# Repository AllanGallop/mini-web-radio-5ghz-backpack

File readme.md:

# Mini Web Radio 3 — 5 GHz Backpack

This project started when the hospital switched off its 2.4 GHz Wi-Fi. The Mini Web Radio was built around an ESP32-S3, which could no longer connect to the network. We also had 200 populated boards already fabricated, so replacing the main board was something I wanted to avoid.

The result is a backpack for [Mini Web Radio v3](https://github.com/AllanGallop/mini-web-radio-3). An ESP32-C5 handles the network connection, while the original S3 keeps doing the audio work. The main PCB, controls and audio hardware all stay in place.

<p align="center">
  
</p>

## Keeping the S3

The S3 had already proved itself in the radio. It could decode the stream, feed the audio output and respond to the controls, with two processor cores and external RAM to help share the work. There was a working design and a working audio stack, so I wanted to keep as much of that as possible.

Unfortunately, its Wi-Fi hardware only supports 2.4 GHz and once that band disappeared from the hospital network, the radio needed another way to connect.

The ESP32-C5 offered the missing connectivity. The question was whether it should replace the S3 or work alongside it.

## Could the C5 do everything?

Replacing the S3 with a C5 would have made for a tidier design, but it would also have meant taking on a much larger software job.

The radio uses [a fork of ESP32-audioI2S](https://github.com/AllanGallop/ESP32-audioI2S), which is designed for multicore ESP32 devices. The C5 has only one app core. It does have a separate low-power processor, but it can't serve as the second application core the audio library expects.

Receiving a stream is only part of the job: the radio also has to buffer and decode it, keep the I²S output supplied, and respond when someone turns the dial. Moving everything onto the C5 would mean porting or replacing the audio stack and working out how to keep those jobs running reliably on one application core.

Memory is another constraint, although it is easy to overstate it. The C5 has less internal SRAM than the S3. Adding RAM can help with buffers; it doesn't make software written for two application cores work on one.

Keeping the S3 and giving the C5 responsibility for handling connectivity and fetching the stream was a more manageable change.

### Separate chips, separate memory

Using both processors doesn't give the radio a single shared pool of RAM. Each chip still has its own memory, and anything needed by the other has to be sent over SPI.

```mermaid
flowchart TB
  subgraph C5["ESP32-C5: network side"]
    CCPU["One application core"]
    CRAM["384 KB internal HP SRAM"]
    CPS["External PSRAM supported"]
    CCPU --- CRAM
    CCPU --- CPS
  end
  subgraph S3["ESP32-S3: audio side"]
    SCPU["Two application cores"]
    SRAM["512 KB internal SRAM"]
    SPS["External PSRAM supported"]
    SCPU --- SRAM
    SCPU --- SPS
  end
  CCPU <-->|"SPI"| SCPU
```

I did consider whether the two chips could share external PSRAM, but coordinating access would have added far too much complexity for this upgrade. Keeping their memory separate and passing the stream over SPI was a much more practical approach.

## Why not attach an SDIO radio?

Another option was to leave the S3 running the whole application and connect a 5 GHz Wi-Fi module over SDIO. That would have avoided changing where the stream was fetched, but getting it into the existing software environment was the sticking point.

The radio is built with PlatformIO and the Arduino framework. An SDIO module needs a host driver, support for the module's firmware, and a way into the networking APIs the application uses. Finding a module with a Linux driver wouldn't solve those problems for this build.

There are supported approaches, including [Espressif's ESP-Hosted](https://github.com/espressif/esp-hosted-mcu), which can connect a C5 over SDIO. Adopting one would still mean getting the host driver, Arduino core, underlying ESP-IDF version and audio dependencies working together.

There was also the question of how much work would remain on the S3. In the conventional hosted arrangement, the external chip handles Wi-Fi while TCP/IP and sockets remain on the host. The S3 would still be fetching the stream and handling HTTP, or TLS where required, alongside decoding and playback. Replacing the native Wi-Fi stack would remove some work too, and the only reliable answer would come from profiling the complete implementation. But it offered less separation of the networking and audio workloads than letting the C5 fetch the stream itself.

The choice of SPI wasn't what made the offload useful. The useful part was being able to hand the networking job to the C5 and give the S3 a stream of compressed audio bytes to play. There would still be two firmware builds and a protocol to maintain, but I could keep the interface focused on what this radio needed and make it easier for other builders to implement.

## Getting the two chips to cooperate

With the work split between the processors, the next problem was keeping audio moving between them. The C5 receives data in bursts from the network and the S3 has to turn it into a continuous audio output.

The backpack connects them over SPI, using `MOSI`, `MISO`, `CLK` and `CS`, with a separate `RDY` line for coordinating transfers. There is no wireless pairing between the chips: they are physically connected by a flex PCB.

The stream crosses that connection while it is still compressed. Decoding happens on the S3, and the resulting PCM samples go to the DAC over I²S.

```mermaid
flowchart TB
  NET["Internet radio stream"]
  subgraph C5["ESP32-C5"]
    WIFI["5 GHz Wi-Fi and network reception"]
    TX["Stream bytes buffered for transfer"]
    WIFI --> TX
  end
  subgraph S3["ESP32-S3"]
    RX["Received stream buffer"]
    DEC["Compressed audio decoder"]
    PCM["PCM output buffers"]
    RX --> DEC --> PCM
  end
  DAC["PCM5102A DAC"]
  AMP["TDA1308 headphone driver"]
  NET --> WIFI
  TX -->|"SPI: one 1033-byte frame"| RX
  TX -.->|"READY while the chunk queue has audio"| RX
  PCM -->|"I²S: PCM samples"| DAC
  DAC -->|"Analogue stereo"| AMP
```

Getting bytes across SPI is only the beginning. A faster clock moves a burst sooner, and it does nothing for a socket that has stopped. The two images have to agree on a fixed transfer, which of those bytes are audio, and what happens when a queue is full or a frame does not check out.

### Keeping the stream moving

An HTTP read, an SPI transfer and an MP3 frame are three different things. The C5 collects stream bytes and packages them for the link; the S3 puts the received audio into a ring buffer for the decoder. Those buffers give each processor some breathing room when the other is busy.

One detail that matters is what `READY` actually means. It tells the S3 that the C5 has queued audio, rather than telling the C5 that the S3 has space. If the S3's ring buffer fills up, the current implementation drops the incoming chunk. When the C5's own queue fills, its HTTP task waits instead, allowing the network connection to slow down.

That distinction is worth making explicit: there is buffering on both sides, but there isn't end-to-end flow control protecting the S3's ring buffer.

### Current limitations

The link checks frames for corruption and tracks sequence gaps, but it doesn't request retransmission of missing audio. A full S3 ring buffer causes a whole chunk to be dropped. Reconnecting the stream also doesn't clear the queued audio or insert a restart marker, so bytes from the previous connection can be followed by bytes from the new one. These are limitations of the current firmware rather than guarantees of seamless recovery.

<details>
<summary>Protocol details: frame layout, queues and recovery</summary>

### SPI frame layout

Both firmware images declare the same packed `Frame`: a 9-byte header followed by a 1024-byte payload. Every SPI transfer clocks all **1033 bytes**, even when only part of the payload contains audio. The `len` field identifies the valid audio bytes; the unused payload is zero-filled.

| Byte offset | Field | Size | Purpose |
| --- | --- | --- | --- |
| 0 | `m0` | 1 byte | Magic value `0xA5` |
| 1 | `m1` | 1 byte | Magic value `0x5A` |
| 2 | `type` | 1 byte | `0x01` for audio |
| 3 | `flags` | 1 byte | Bit 0: Wi-Fi connected; bit 1: C5 awake |
| 4–5 | `len` | 2 bytes | Valid audio length, up to 1024 bytes |
| 6 | `seq` | 1 byte | Rolling sequence number |
| 7–8 | CRC | 2 bytes | CRC-16-CCITT |
| 9–1032 | `payload` | 1024 bytes | `len` audio bytes followed by zero padding |

The header is little-endian. `m0` and `m1` are `0xA5` and `0x5A`. `type` is `0x01` for audio. `flags` has Wi-Fi connected in bit 0 and C5 awake in bit 1; this C5 image sets the awake bit on every frame. `len` is a `uint16`, clamped to 1024. `seq` is a free-running `uint8`. The CRC-16-CCITT, polynomial `0x1021`, init `0xFFFF`, covers `type` through `seq` and `payload[0..len)`. The magic bytes sit outside it. There is no shared header between the two PlatformIO projects. The structs match because both copies were written to match.

### Buffer ownership and transfer timing

The C5 chunk queue uses static RAM: 31 KiB of payload waiting to be packetised, plus a length field on each slot. The DMA heap is only the three slave buffers. The slave keeps all three transactions queued, including when the chunk queue is empty. Those idle frames go out with `len = 0`, a valid CRC, and a new `seq`. `READY` is high only while `q` is not empty. The S3 sleeps on that pin and clocks a frame only while it stays high. A zero-length frame writes nothing into the ring. Up to three of them can already be armed when audio shows up, so the first clocks after `READY` rises can be empty frames that were filled earlier. They cost a transaction. The pin lags the other way too: popping the last chunk drops `READY` before that frame has necessarily been clocked, so a filled frame can sit in the slave queue until the next rise. It is not dropped.

`READY` means the C5 has a chunk. It does not mean the S3 has room. If the 128 KiB ring cannot hold `len` bytes, the S3 drops the whole chunk and counts the drop. The C5 is not told. Backpressure toward the server happens on the C5 queue instead: a full `q` makes the HTTP task wait 2 ms and retry the same bytes, which stalls the socket rather than discarding them.

A bad magic, an unexpected type, or a bad CRC is discarded before the ring. A gap in `seq` is counted, and the frame is kept. Wi-Fi state is a flag at the moment `fill_frame` runs. The S3 uses it for the Wi-Fi LED. It does not flush the ring when the flag clears, when the socket drops, or when `seq` restarts after a C5 reboot. Audio already queued is still played. On a dead stream the C5 closes the socket, waits, and issues the HTTP GET again. Whatever is still in `q` is sent first, then the new body, with no resync marker between them.

</details>

Configuration follows the same division. The C5 now joins the Wi-Fi network and fetches the stream, so that is where the network credentials and stream address belong. Updating the original S3 settings alone won't configure the backpack.

## Fitting it to the existing board

The hardware had to fit around a radio that was already built. There was no spare footprint for another module, and replacing the main PCB would have defeated much of the point of making an upgrade.

A flexible PCB let me put the C5 on the back of the board and fold the connections around to the S3. It takes care of the signal routing, with separate wires for power and ground.

<p align="center">
  
</p>

That leaves the DAC, headphone driver, controls and main PCB in place. The flex is an unusual shape when laid flat, but makes more sense once it is wrapped around the board.

<p align="center">
  
</p>

<p align="center">
  
</p>

Fitting the module was only part of it. The 3.3 V supply also has to support another Wi-Fi device, the signal connections need to remain reliable, and the antenna needs suitable clearance. Those constraints still apply even when the extra hardware fits neatly into the case.

## Hardware

The [hardware directory](hardware/) contains the Eagle board and schematic files, plus [Gerbers](hardware/gerber.zip).

Connect the backpack's **3V3** pad to the `ASO` LDO regulator's 3.3 V output, and **GND** to a suitable via in the main board's ground pour. Refer to the schematic and build photographs for placement.

<p align="center">
  
</p>

## Firmware

Both boards need the backpack firmware built and uploaded. **This prototype does not include the previous configuration provisions.** The settings and stream formats available in the original v3 firmware should not be assumed to be supported here.

### Mini Web Radio v3 (S3)

1. Open `firmware/S3` in PlatformIO.
2. Build.
3. Upload to the S3.

### Backpack (C5)

1. Open `firmware/C5` in PlatformIO.
2. Edit `main.cpp`:
   * Set `WIFI_SSID` and `WIFI_PASS` for your Wi-Fi network.
   * Set `HOST`, `PORT` and `PATH` for your audio stream.
3. Build.
4. Upload to the C5.

## Where this leaves the radio

The backpack is a compromise, but it lets the existing radio connect to 5 GHz without replacing the board or starting again with the audio software. The cost is another processor and a communication link; the benefit is keeping the parts of the design that already work.

A future version could bring both jobs back onto one suitably supported chip. For now, the C5 gets the stream and the S3 plays it, which is what the radio needed to do in the first place.

 <br>
Thanks to my Makerspace - For putting up with my antics :D

## Technical references

- [Mini Web Radio v3 hardware and firmware](https://github.com/AllanGallop/mini-web-radio-3)
- [Audio-library fork used by v3, including its multicore requirement](https://github.com/AllanGallop/ESP32-audioI2S)
- [Espressif ESP-Hosted coprocessor networking](https://github.com/espressif/esp-hosted-mcu)
- [ESP-Hosted MCU guide, including the host networking stack](https://github.com/espressif/esp-hosted-mcu/blob/main/docs/getting-started-mcu.md)
- [Espressif ESP32-S3 overview](https://www.espressif.com/products/socs/esp32-s3)
- [Espressif ESP32-C5-WROOM-1 / WROOM-1U datasheet](https://documentation.espressif.com/esp32-c5-wroom-1_wroom-1u_datasheet_en.html)

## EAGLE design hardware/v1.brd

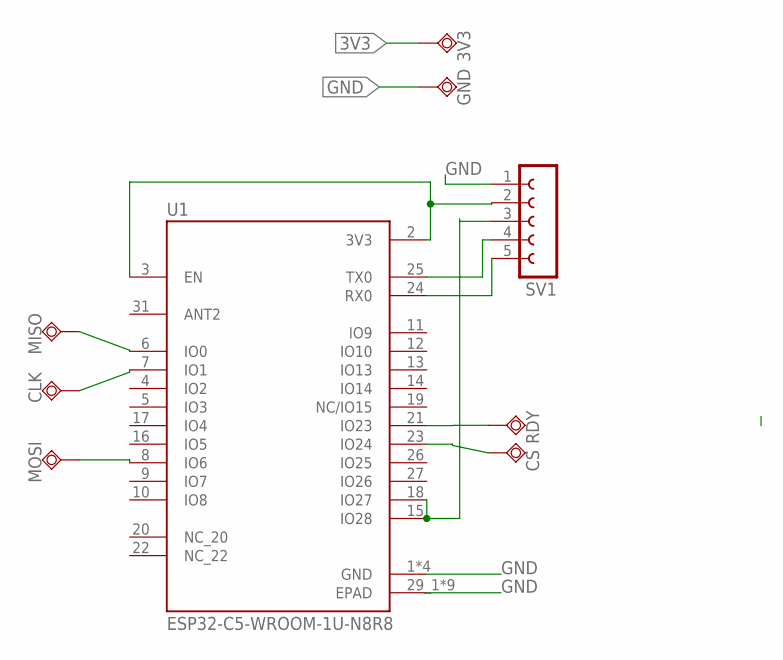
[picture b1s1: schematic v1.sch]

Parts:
3V3: TPSQTP09SQ; TP09SQ
CLK: TPSQTP09SQ; TP09SQ
CS: TPSQTP09SQ; TP09SQ
GND: TPSQTP09SQ; TP09SQ
MISO: TPSQTP09SQ; TP09SQ
MOSI: TPSQTP09SQ; TP09SQ
RDY: TPSQTP09SQ; TP09SQ
SV1: FE05-1
U1: ESP32-C5-WROOM-1U-N8R8; XCVR_ESP32-C5-WROOM-1U-N8R8

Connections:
3V3: 3V3.TP, SV1.2, U1.2 (3V3), U1.3 (EN)
GND: GND.TP, SV1.1, U1.1 (GND), U1.28 (GND), U1.29_1 (EPAD), U1.29_2 (EPAD), U1.29_3 (EPAD), U1.29_4 (EPAD), U1.29_5 (EPAD), U1.29_6 (EPAD), U1.29_7 (EPAD), U1.29_8 (EPAD), U1.29_9 (EPAD), U1.30 (GND), U1.32 (GND)
unnamed: RDY.TP, U1.21 (IO23)
unnamed: CS.TP, U1.23 (IO24)
unnamed: MISO.TP, U1.6 (IO0)
unnamed: CLK.TP, U1.7 (IO1)
unnamed: SV1.3, U1.15 (IO28), U1.18 (IO27)
unnamed: MOSI.TP, U1.8 (IO6)
unnamed: SV1.5, U1.24 (RX0)
unnamed: SV1.4, U1.25 (TX0)

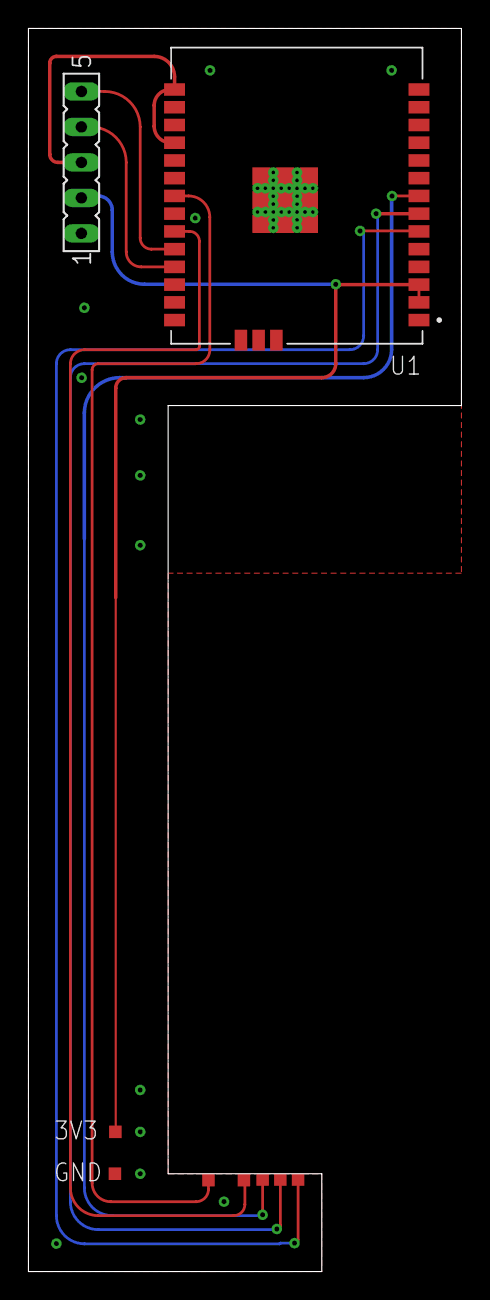
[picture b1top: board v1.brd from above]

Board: 2 copper layers, 31.0 x 89.0 mm, 9 parts (0 on the bottom side), 10 nets.

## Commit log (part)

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2026-01-20 add readme
